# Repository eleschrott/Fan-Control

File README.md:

# Fan-Control
### Controls by temperature the speed of a fan driven with PWM
***
This small project is intended for cooling situations where the focus is on maximum noise reduction. To achieve this goal, the temperature is measured with a sensor (LM35DT) and processed by a microcontroller. This µController generates a pulse width modulated signal with 32kHz for a fan. The duty cycle of this PWM is directly proportional to the measured temperature.

Only a few parts are needed. The software can be realized with the Arduino IDE or ohters. I use Visual Studio with the <br>[Visual Micro Plugin](https://www.visualmicro.com/), but also Atmel Studio or others should working well. Here we use an Atmel ATtiny85, but other types with at least one analog input and a PWM capable output are also suitable.
The program is small enough to work on narrow-breasted microcontrollers. Only an internal clock frequency of 8MHz is necessary to output the PWM signal at 32kHz. This frequency is necessary, because some fans tend to produce an unpleasant whistling sound at low frequencies. The controlled temperature range is between 20 and 150 degrees Celsius.

The example shown here, refers to an ATtiny85 from Atmel. For other types or manufacturers other fuses may be set. These can be found in the respective documentations of the µController.

[Circuit diagram and board layout](/KiCAD/Fancontrol) are also included, these files are created with [KiCad](https://kicad-pcb.org/).
***
For the hardware you need the following (fits on the attached board layout):
+ Atmel ATtiny85 or similar (SOIC-8)
+ Board mounted Temperature Sensor LM35DT (TO220) 
+ Darlington transistor TIP122 (TO220)
+ Diode 1N4007 (THT)
+ Resistors: 1k, 10k (SMD 0805)
+ Capacitors: 100n, 10µ (SMD 0603)
+ Connectors: 1x 2Pin, 1x 3Pin, 1x 4Pin (THT)
+ Pinheader 02x03 Pins (THT)
+ 12V DC fan

The project requires two DC voltages, 5V for the µController and 12V for the fan. The power consumption at 12V depends on the fan type. The control needs very little current (max.12mA). In order to cope with an increased power consumption of the fan, it is recommended to provide the transistor with a heat sink. At low current consumption, the transistor can be operated without.
The circuit board is designed in such a way that the transistor is soldered in reverse, with the front side lying on the board, so that the heat sink I have in stock, can be mounted as flat as possible.

The parts I used for the circuit board were still available in my workshop. Of course, the used parts can vary in size and shape. It is only important that the microcontroller used, harmonizes with the software and that the peripherals can be controlled safely.
***
The circuit diagram is quite clear and does not require any great explanation. 

***

In order to define the ranges for the control, the header file **Fancontrol.h** contains some constants, which can be adapted to the respective requirements.

```c
// Temperature values to define the ranges.
// We use no float variables, all temperatures gets calculated in 16Bit uint16_t!
// This means a value of 2350 corresponds to a temperature of 23.50 degrees Celsius
constexpr auto TEMP_MINHYS  = 2350; // Hysteresis for minimum temp to switch off the running fan
constexpr auto TEMP_MIN     = 2500; // Minimum Temp to switch on the fan
constexpr auto TEMP_NORMHYS = 2850; // Hysteresis for temp to switch normal range off
constexpr auto TEMP_NORM    = 3000; // Start of normal range
constexpr auto TEMP_MID     = 5000; // Temp to go to high range
constexpr auto TEMP_MAX     = 7500; // Max temperature
constexpr auto TEMP_OFFSET  =   15; // Minimum integer offset, from which a temperature control
                                    // becomes effective, default is 15 -> 0.15 degree.
```

There are also constants for the adaptation of the used fan. Not every fan runs with the same PWM values.
```c
// Fan responsible parameter to run the fan in smooth and low noise as possible
// Adjust this values to your fan model!
constexpr auto FAN_OFF      =   0; // PWM 0 -> Fan off!
constexpr auto FAN_LOWLOW   =  63; // Lowest PWM to run the fan save on minimum noise
constexpr auto FAN_LOW      =  75; // Minimum for controlled "normal" run
constexpr auto FAN_MID      = 150; // Maximum for controlled normal run and minimum for high speed run
constexpr auto FAN_HIGH     = 255; // Maximum for controlled high speed
constexpr auto FAN_OFFSET   =   2; // Minimum integer offset, from which a PWM regulation
                                   // becomes effective, default is 2 -> ~ 0.8%. 
```
***
To get this project working with the Arduino IDE, you need to install a board file to give the IDE knowledge about the ATtiny. Here you can find it: https://github.com/SpenceKonde/ATTinyCore.
To operate the µController with 8MHz some fuses must be set. For the Arduino IDE, this is described in the file [How2SetCPUFuses.txt](/Arduino/FanControl/How2SetCPUFuses.txt).

On the web site [Engbedded](http://www.engbedded.com/fusecalc) you can find a "AVR Fuse Calculator". Here you can verify the Low, High and Extended fuses.
```
avrdude: safemode: lfuse reads as E2
avrdude: safemode: hfuse reads as D7
avrdude: safemode: efuse reads as FF
```

***
ISP is used to program the microcontroller. It is also possible to flash the µcontroller before soldering and omit the pin headers for ISP. For adjustments to the program it is recommended to mount the 6pin header.
***

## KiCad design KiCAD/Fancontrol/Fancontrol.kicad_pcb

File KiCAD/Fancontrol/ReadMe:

Files for KiCad 5.1.5

It is not necessary to have a two-sided circuit board. If you want to make the circuit board yourself, one layer is perfectly sufficient.
The layout included here is single sided, the top side consists only of a groundplane.

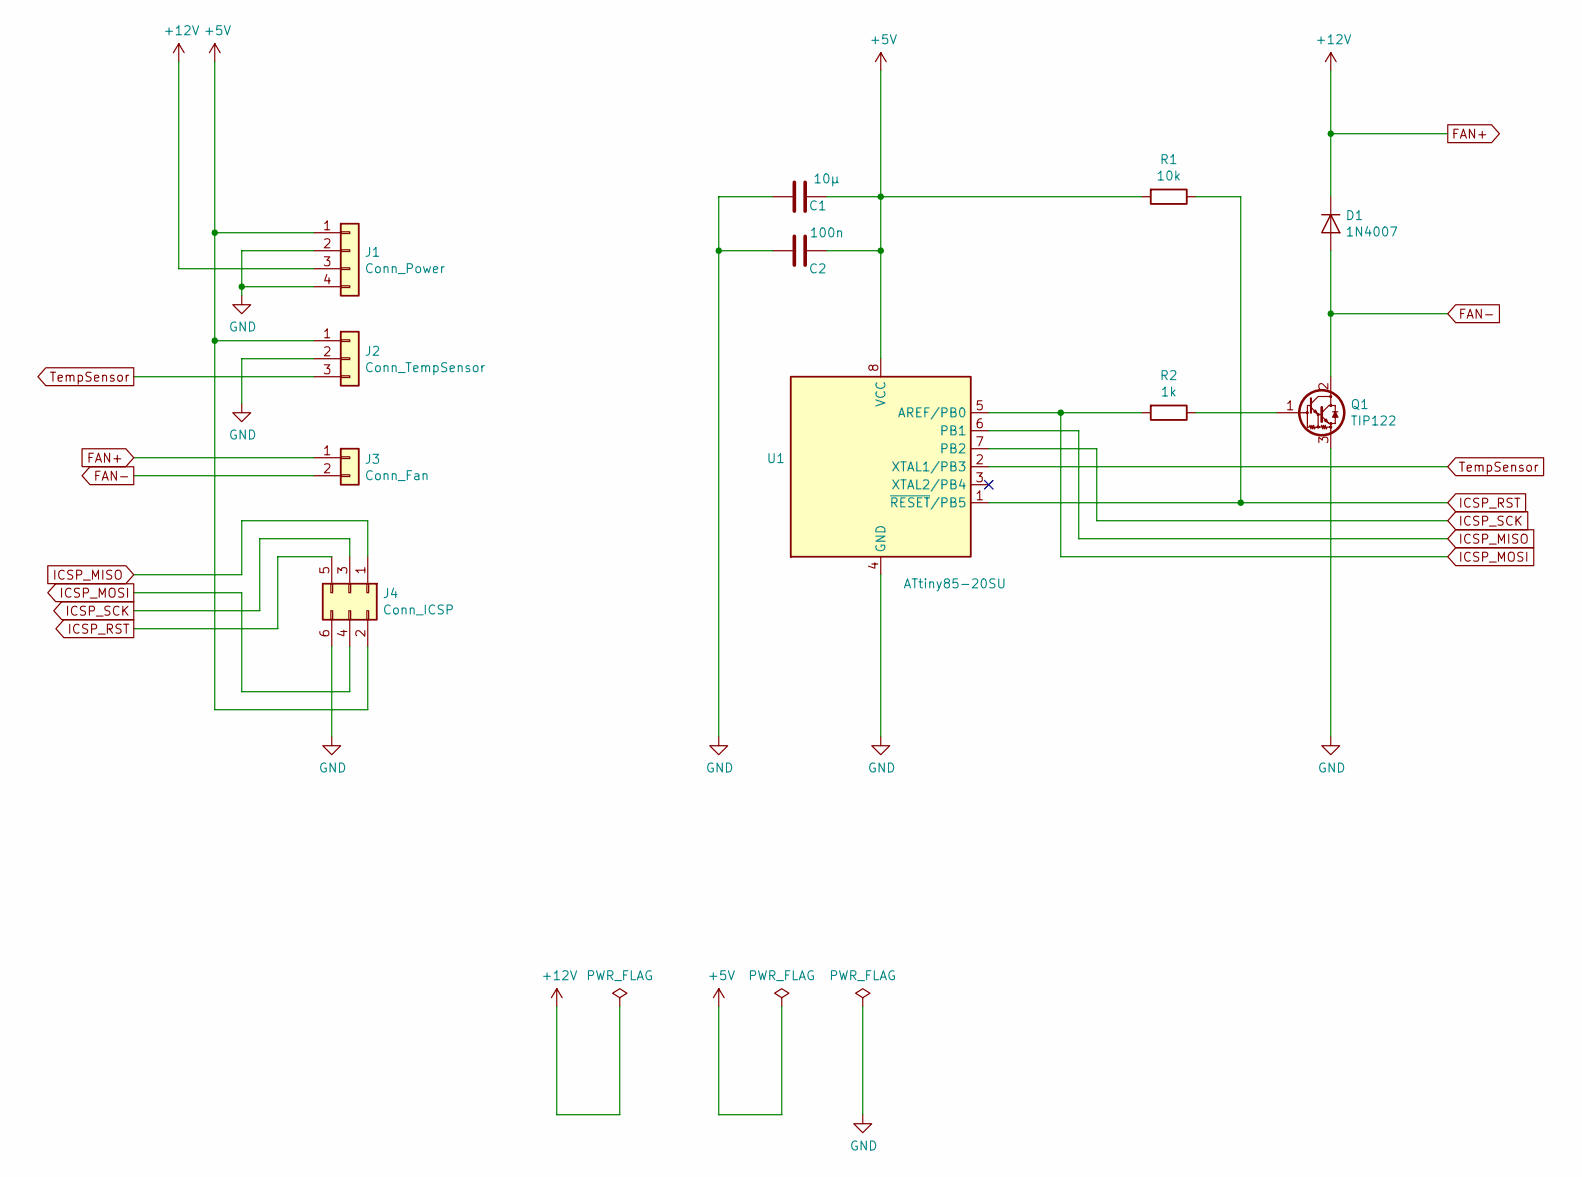
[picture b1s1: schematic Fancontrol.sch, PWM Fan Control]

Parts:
C1: 10µ; C_0603_HandSoldering
C2: 100n; C_0603_HandSoldering
D1: 1N4007; D_DO-41_SOD81_P10.16mm_Horizontal
J1: Conn_Power; Socket_MOLEX-KK-RM2-54mm_Lock_4pin_straight
J2: Conn_TempSensor; Socket_MOLEX-KK-RM2-54mm_Lock_3pin_straight
J3: Conn_Fan; Socket_MOLEX-KK-RM3-96mm_Lock_2pin_straight
J4: Conn_ICSP; Pin_Header_Straight_2x03_Pitch2.54mm
Q1: TIP122; TO-220-3_Vertical
R1: 10k; R_0805_HandSoldering
R2: 1k; R_0805_HandSoldering
U1: ATtiny85-20SU; SOIC127P798X216-8N

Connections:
+5V: C1.1, C2.1, J1.1, J2.1, J4.2, R1.2, U1.8 (VCC)
FAN+: D1.1 (K), J1.3, J3.1
FAN-: D1.2 (A), J3.2, Q1.2 (C)
GND: C1.2, C2.2, J1.2, J1.4, J2.2, J4.6, Q1.3 (E), U1.4 (GND)
ICSP_MISO: J4.1, U1.6 (PB1)
ICSP_MOSI: J4.4, R2.2, U1.5 (AREF/PB0)
ICSP_RST: J4.5, R1.1, U1.1 (~RESET~/PB5)
ICSP_SCK: J4.3, U1.7 (PB2)
unnamed: Q1.1 (B), R2.1
TempSensor: J2.3, U1.2 (XTAL1/PB3)

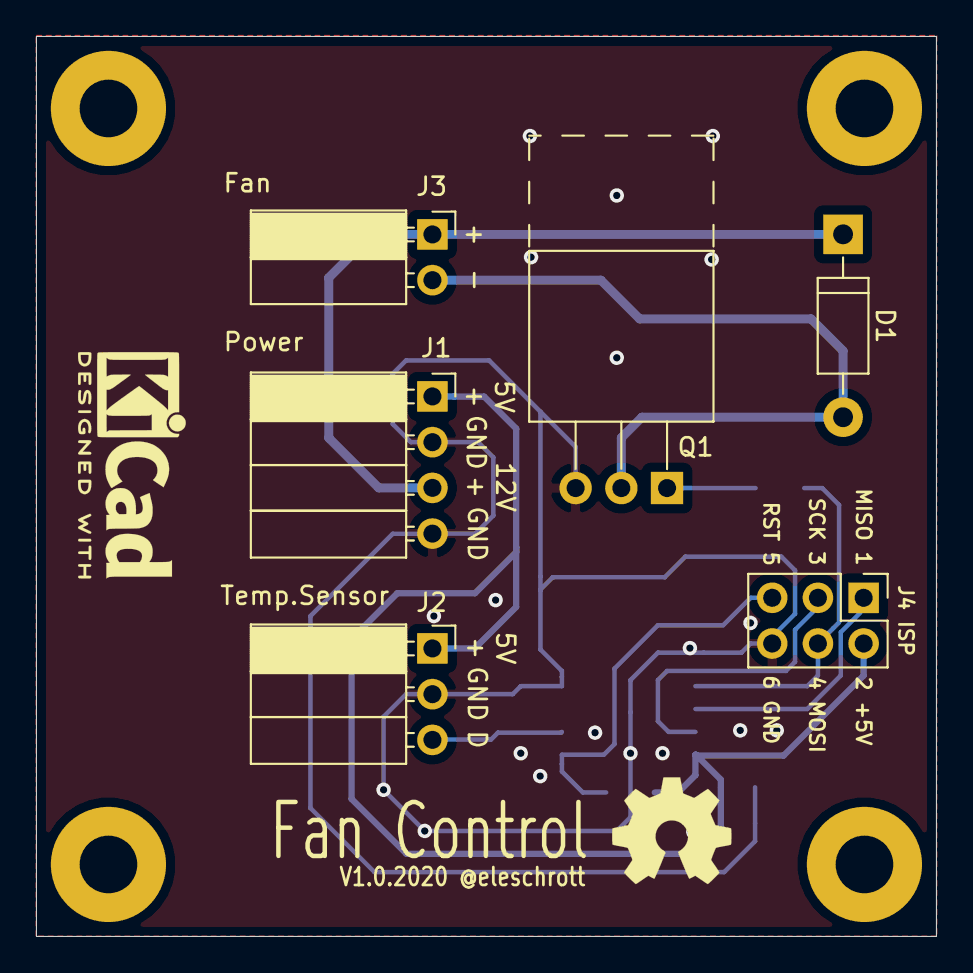
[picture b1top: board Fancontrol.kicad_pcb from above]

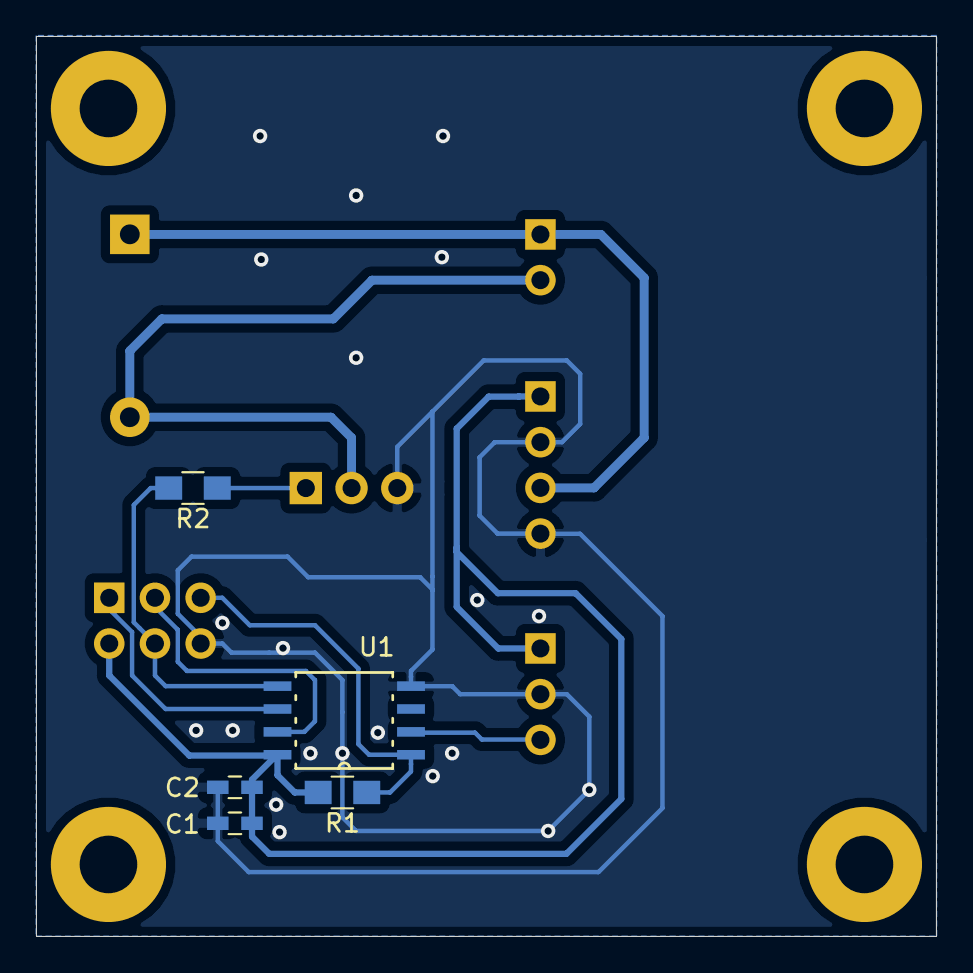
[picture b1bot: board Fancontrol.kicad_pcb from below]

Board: 2 copper layers, 50.0 x 50.0 mm, 11 parts (5 on the bottom side), 10 nets.

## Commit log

2020-01-28 Create . Arduino
2020-01-28 Create . ...
2020-01-28 Create . ..
2020-01-28 Add text about sensor to schematic
2020-01-28 Change size of picture
2020-01-28 Update version
2020-01-29 Update capacitor C1
2020-01-31 add brackets to the macro SetPWM32kHz()
2020-02-02 Add VisualMicro headerfile
2020-02-02 Update file path
2020-02-02 Create ...
2020-02-02 Disable the millis()/micros() selection
    The delay()-function only works, if this is disbaled.
2020-02-04 Add offsets
    Offset for the temperature control and the PWM regulation added.
2020-02-04 Add offset calculation
    Added calculations with offsets for temperature and PWM
2020-02-04 Add offsets
    Added offsets for temperature control and pwm calculation
2020-02-04 Add offset calculations
    Added calculations with offsets for temperature control and PWM calculation
2020-02-07 Change size
2020-02-10 Add check of "fan off"
2020-02-10 Add links to KiCad
2020-02-18 Erase obsolete fan on/off on setup()
2020-02-26 TEMP_OFFSET fixed
2020-02-26 Fixed variable _speed in Workaround
